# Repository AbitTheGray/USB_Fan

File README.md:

# USB Fan

Single-cell USB Fan with voltage selection and USB-C Charger built around `TP4056`+`DW01A` and `TPS61170`.

**This board is untested.**

Designed to be manufactured by [JLCPCB](https://jlcpcb.com/) as 4layer PCB.
*It is not possible to manufacture as 2layer PCB.*

## Features

- 4 fan voltages (5V / 9V / 12V / 24V)
  - Select **before** turning the SW1 on
- USB-C charging
  - 5V 1.5A max (5.1k resistors)
  - `TP4056` charger
    - Status LEDs
      - Red = Charging
      - Blue = Standby
    - 1S 1A charging (1 cell in series, unlimited in parallel)
  - 1.5A discharge (`DW01A`)
- Power-on switch
  - Only affects the output, battery can still charge
  - **Do not turn on when charging**
  - Minimum current runs through the switch
    - No special switch needed
    - It is not a toggle!

### Warnings

- There are no reverse-polarity protections
  - Not on battery or USB-C
- `D3`+`D4` don't have JLCPCB part number, pick any `1206` LEDs you like
- Default component placement has to be tweaked on JLCPCB online editor
  - `J1` shifted to right position
  - `L1` rotated 90deg
  - `U1`, `U2`, `U3` and `U4` must be rotated so 1st pin is in the corner with long line on Stencil layer
    - `U1` = top right, `U2` = top left, `U3` = bottom right, `U4` = top left

## TODO

- Power LED (white) ?
- Add assembly tooling holes

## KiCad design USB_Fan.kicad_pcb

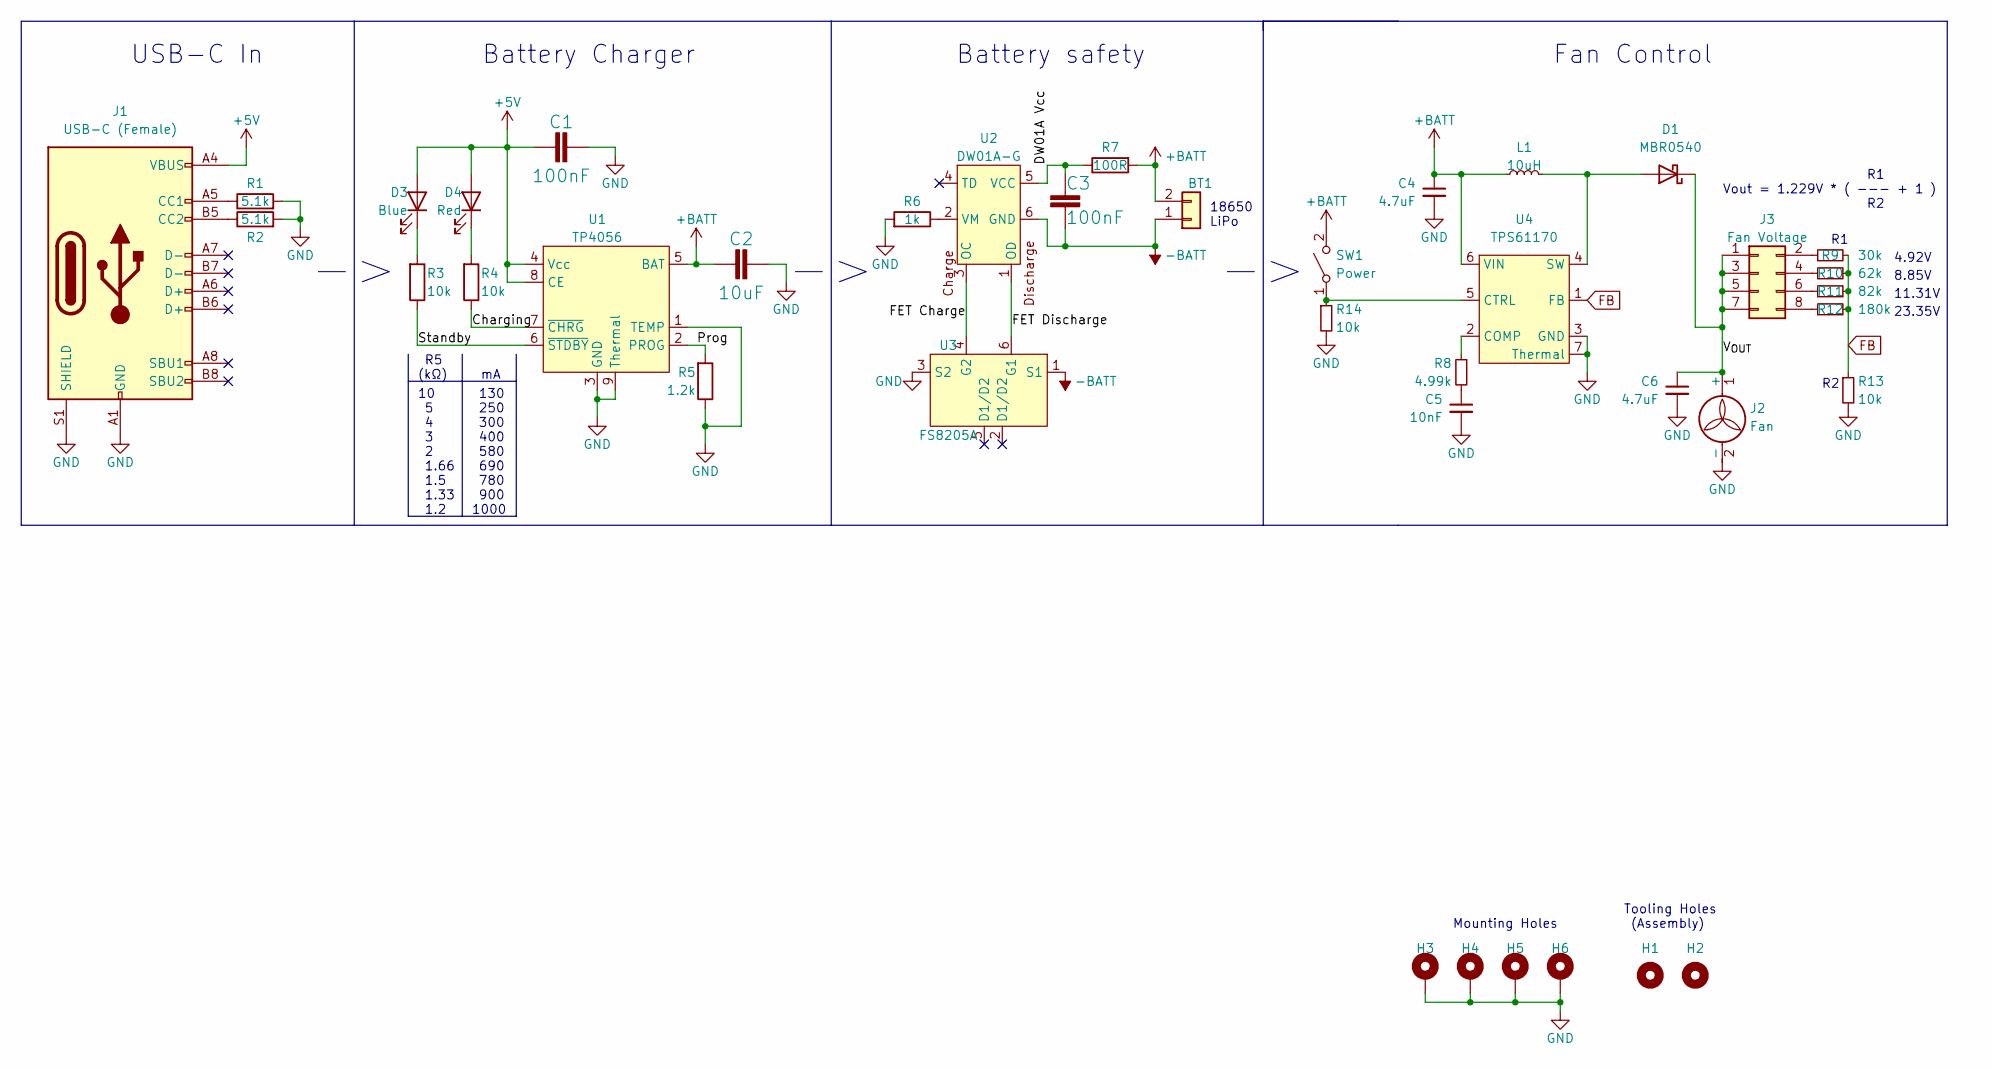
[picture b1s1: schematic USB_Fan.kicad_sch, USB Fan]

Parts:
BT1: Conn_01x02; JST_PH_B2B-PH-K_1x02_P2.00mm_Vertical; LCSC C18077744
C1, C3: 100nF; C_0603_1608Metric; LCSC C14663
C2: 10uF; C_0603_1608Metric; LCSC C96446
C4, C6: 4.7uF; C_0603_1608Metric; LCSC C19666
C5: 10nF; C_0603_1608Metric; LCSC C57112
D1: MBR0540; D_SOD-123; LCSC C116159
D3: Blue; LED_1206_3216Metric; LCSC C965827
D4: Red; LED_1206_3216Metric; LCSC C2827254
H1, H2: MountingHole_Pad; JLCPCB ToolingHole
H3, H4, H5, H6: MountingHole_Pad; MountingHole_2.2mm_M2_ISO7380_Pad
J1: USB-C (Female); USB_C_Receptacle_GCT_USB4105-xx-A_16P_TopMnt_Horizontal; LCSC C2765186
J2: Fan; FanPinHeader_1x03_P2.54mm_Vertical; LCSC C234181
J3: Fan Voltage; PinHeader_2x04_P2.54mm_Vertical
L1: 10uH; Inductor 4x4; LCSC C497803
R1, R2: 5.1k; R_0603_1608Metric; LCSC C23186
R3, R4, R13, R14: 10k; R_0603_1608Metric; LCSC C25804
R5: 1.2k; R_0603_1608Metric; LCSC C22765
R6: 1k; R_0603_1608Metric; LCSC C21190
R7: 100R; R_0603_1608Metric; LCSC C22775
R8: 4.99k; R_0603_1608Metric; LCSC C2988946
R9: 30k; R_0603_1608Metric; LCSC C22984
R10: 62k; R_0603_1608Metric; LCSC C23221
R11: 82k; R_0603_1608Metric; LCSC C23254
R12: 180k; R_0603_1608Metric; LCSC C22827
SW1: Power; PinHeader_1x02_P2.54mm_Vertical
U1: TP4056; HSOP-8-1EP_3.9x4.9mm_P1.27mm_EP2.41x3.1mm_ThermalVias; LCSC C16581
U2: DW01A-G; SOT-23-6; LCSC C351410
U3: FS8205A; SOT-23-6; LCSC C908265
U4: TPS61170; DFN-6-1EP_2x2mm_P0.65mm_EP1.01x1.7mm; LCSC C15163

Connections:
+5V: C1.1, D3.2 (A), D4.2 (A), J1.A4 (VBUS), J1.A9 (VBUS), J1.B4 (VBUS), J1.B9 (VBUS), U1.4 (Vcc), U1.8 (CE)
+BATT: BT1.2, C2.1, C4.1, L1.1, R7.2, SW1.2 (B), U1.5 (BAT), U4.6 (VIN)
-BATT: BT1.1, C3.2, U2.6 (GND), U3.1 (S1)
/Charging: R4.1, U1.7 (~CHRG)
/DW01A Vcc: C3.1, R7.1, U2.5 (VCC)
/FET Charge: U2.3 (OC), U3.4 (G2)
/FET Discharge: U2.1 (OD), U3.6 (G1)
/Prog: R5.2, U1.2 (PROG)
/Standby: R3.1, U1.6 (~STDBY)
/V_{OUT}: C6.1, D1.1 (K), J2.1 (+), J3.1, J3.3, J3.5, J3.7
FB: R9.2, R10.2, R11.2, R12.2, R13.1, U4.1 (FB)
GND: C1.2, C2.2, C4.2, C5.2, C6.2, H3.1, H4.1, H5.1, H6.1, J1.A1 (GND), J1.A12 (GND), J1.B1 (GND), J1.B12 (GND), J1.S1 (SHIELD), J2.2 (-), R1.2, R2.2, R5.1, R6.2, R13.2, R14.2, U1.1 (TEMP), U1.3 (GND), U1.9 (Thermal), U3.3 (S2), U4.3 (GND), U4.7 (Thermal)
unnamed: C5.1, R8.2
unnamed: D1.2 (A), L1.2, U4.4 (SW)
unnamed: D3.1 (K), R3.2
unnamed: D4.1 (K), R4.2
unnamed: J1.A5 (CC1), R1.1
unnamed: J1.B5 (CC2), R2.1
unnamed: J3.2, R9.1
unnamed: J3.4, R10.1
unnamed: J3.6, R11.1
unnamed: J3.8, R12.1
unnamed: R14.1, SW1.1 (A), U4.5 (CTRL)
unnamed: R6.1, U2.2 (VM)
unnamed: R8.1, U4.2 (COMP)

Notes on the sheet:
8.85V
130 250 300 400 580 690 780 900 1000
18650 LiPo
USB-C In
R5 (kΩ)
Tooling Holes (Assembly)
Fan Control
10 5 4 3 2 1.66 1.5 1.33 1.2
Battery Charger
R1 Vout = 1.229V * ( --- + 1 ) R2
Battery safety
11.31V
Mounting Holes
4.92V
23.35V

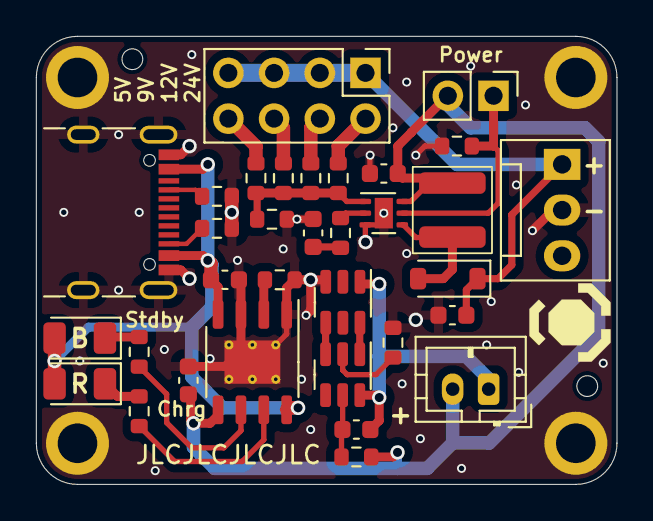
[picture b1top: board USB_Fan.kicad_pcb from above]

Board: 4 copper layers, 32.3 x 24.9 mm, 39 parts (0 on the bottom side), 25 nets.

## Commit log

2023-09-21 Initial version
2023-09-29 Fix problems on the PCB
2023-10-01 Add tooling holes
2023-10-01 Minor tweaks to the PCB
2024-03-16 KiCad 8
2024-03-24 Labels
2024-06-13 Revision 2
2025-01-14 Minor tweak for manufacturing
